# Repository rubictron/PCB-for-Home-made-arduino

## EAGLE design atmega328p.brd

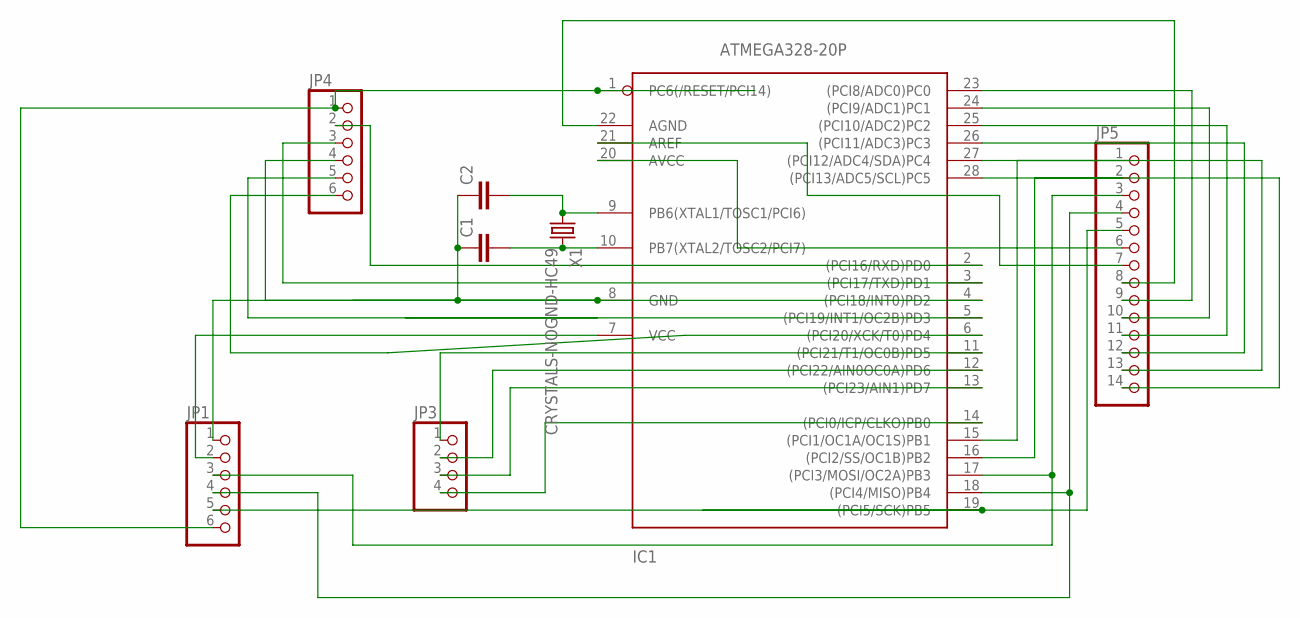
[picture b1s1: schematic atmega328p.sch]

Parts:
C1: C5/2.5; C5B2.5
C2: C2.5/2; C2.5-2
IC1: ATMEGA328-20P; DIL28-3
JP1, JP4: PINHD-1X6; 1X06
JP3: PINHD-1X4; 1X04
JP5: PINHD-1X14; 1X14
X1: CRYSTALS-NOGND-HC49; HC49

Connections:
unnamed: IC1.7 (VCC), JP1.2
unnamed: IC1.2 ((PCI16/RXD)PD0), JP4.2
unnamed: C2.2, IC1.9 (PB6(XTAL1/TOSC1/PCI6)), X1.1
unnamed: C1.2, IC1.10 (PB7(XTAL2/TOSC2/PCI7)), X1.2
unnamed: C1.1, C2.1, IC1.8 (GND), JP1.1
unnamed: IC1.3 ((PCI17/TXD)PD1), JP4.3
unnamed: IC1.1 (PC6(/RESET/PCI14)), JP1.6, JP4.1
unnamed: IC1.17 ((PCI3/MOSI/OC2A)PB3), JP1.3, JP5.3
unnamed: IC1.19 ((PCI5/SCK)PB5), JP1.5, JP5.5
unnamed: IC1.4 ((PCI18/INT0)PD2), JP4.4
unnamed: IC1.5 ((PCI19/INT1/OC2B)PD3), JP4.5
unnamed: IC1.6 ((PCI20/XCK/T0)PD4), JP4.6
unnamed: IC1.11 ((PCI21/T1/OC0B)PD5), JP3.1
unnamed: IC1.12 ((PCI22/AIN0OC0A)PD6), JP3.2
unnamed: IC1.13 ((PCI23/AIN1)PD7), JP3.3
unnamed: IC1.14 ((PCI0/ICP/CLKO)PB0), JP3.4
unnamed: IC1.15 ((PCI1/OC1A/OC1S)PB1), JP5.1
unnamed: IC1.16 ((PCI2/SS/OC1B)PB2), JP5.2
unnamed: IC1.23 ((PCI8/ADC0)PC0), JP5.9
unnamed: IC1.24 ((PCI9/ADC1)PC1), JP5.10
unnamed: IC1.21 (AREF), JP5.7
unnamed: IC1.25 ((PCI10/ADC2)PC2), JP5.11
unnamed: IC1.26 ((PCI11/ADC3)PC3), JP5.12
unnamed: IC1.27 ((PCI12/ADC4/SDA)PC4), JP5.13
unnamed: IC1.28 ((PCI13/ADC5/SCL)PC5), JP5.14
unnamed: IC1.20 (AVCC), JP5.6
unnamed: IC1.22 (AGND), JP5.8
unnamed: IC1.18 ((PCI4/MISO)PB4), JP1.4, JP5.4

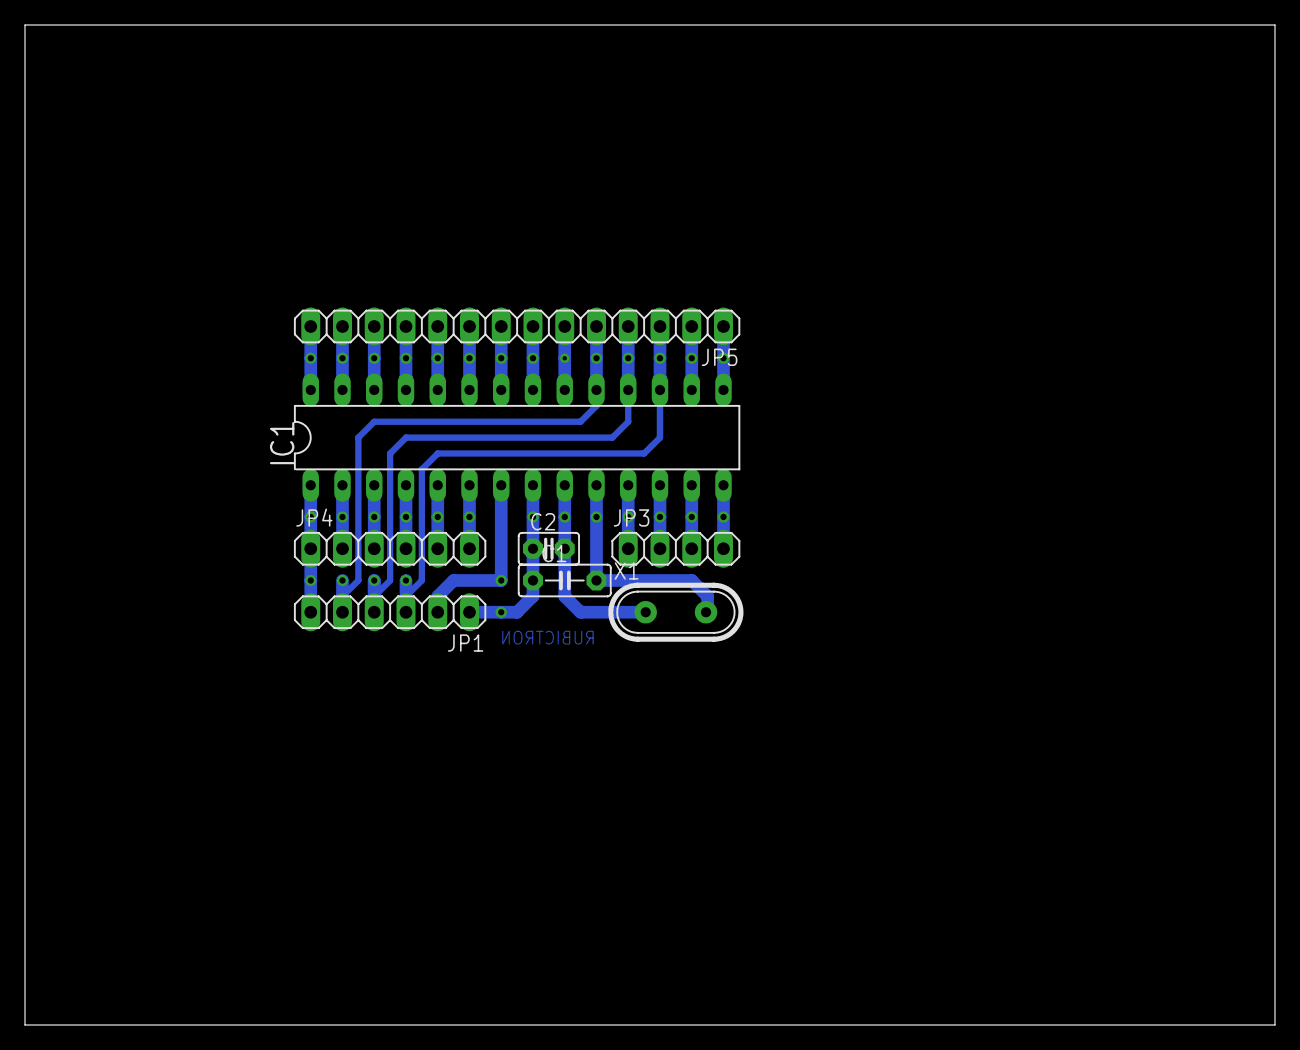
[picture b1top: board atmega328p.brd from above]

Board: 2 copper layers, 100.0 x 80.0 mm, 8 parts (0 on the bottom side), 28 nets.

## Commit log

2018-04-04 add readme
2018-04-06 with PCB bord
2018-04-06 modified: atmega328p.brd
2018-05-03 without top layer
2018-05-03 with pdf
